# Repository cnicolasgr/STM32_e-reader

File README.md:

# STM32_e-reader
A modest attempt to build an e-reader using a stm32MP1.

> [!CAUTION]
> THIS IS A WORK IN PROGRESS. HACK AROUND AT YOUR OWN RISK.
> I didn't test the board yet and can't be held responsible for any magic smoke 💨

I'm planning to use the [KOReader](https://github.com/koreader/koreader) on OpenSTLinux for the software side, and a modified [epdiy](https://github.com/vroland/epdiy/) driver board for the hardware.
The first version will be using a ED060XC3 screen with a TMA340 touch screen.

Here is the test board:

based on these PCBs from [@martinberlin](https://github.com/martinberlin):

* [epdiy-hardware-versions/versions](https://github.com/martinberlin/epdiy-hardware-versions/tree/main/versions)
* [epdiy-hardware-versions/epdiy-v7-raw](https://github.com/martinberlin/epdiy-hardware-versions/tree/main/epdiy-v7-raw)

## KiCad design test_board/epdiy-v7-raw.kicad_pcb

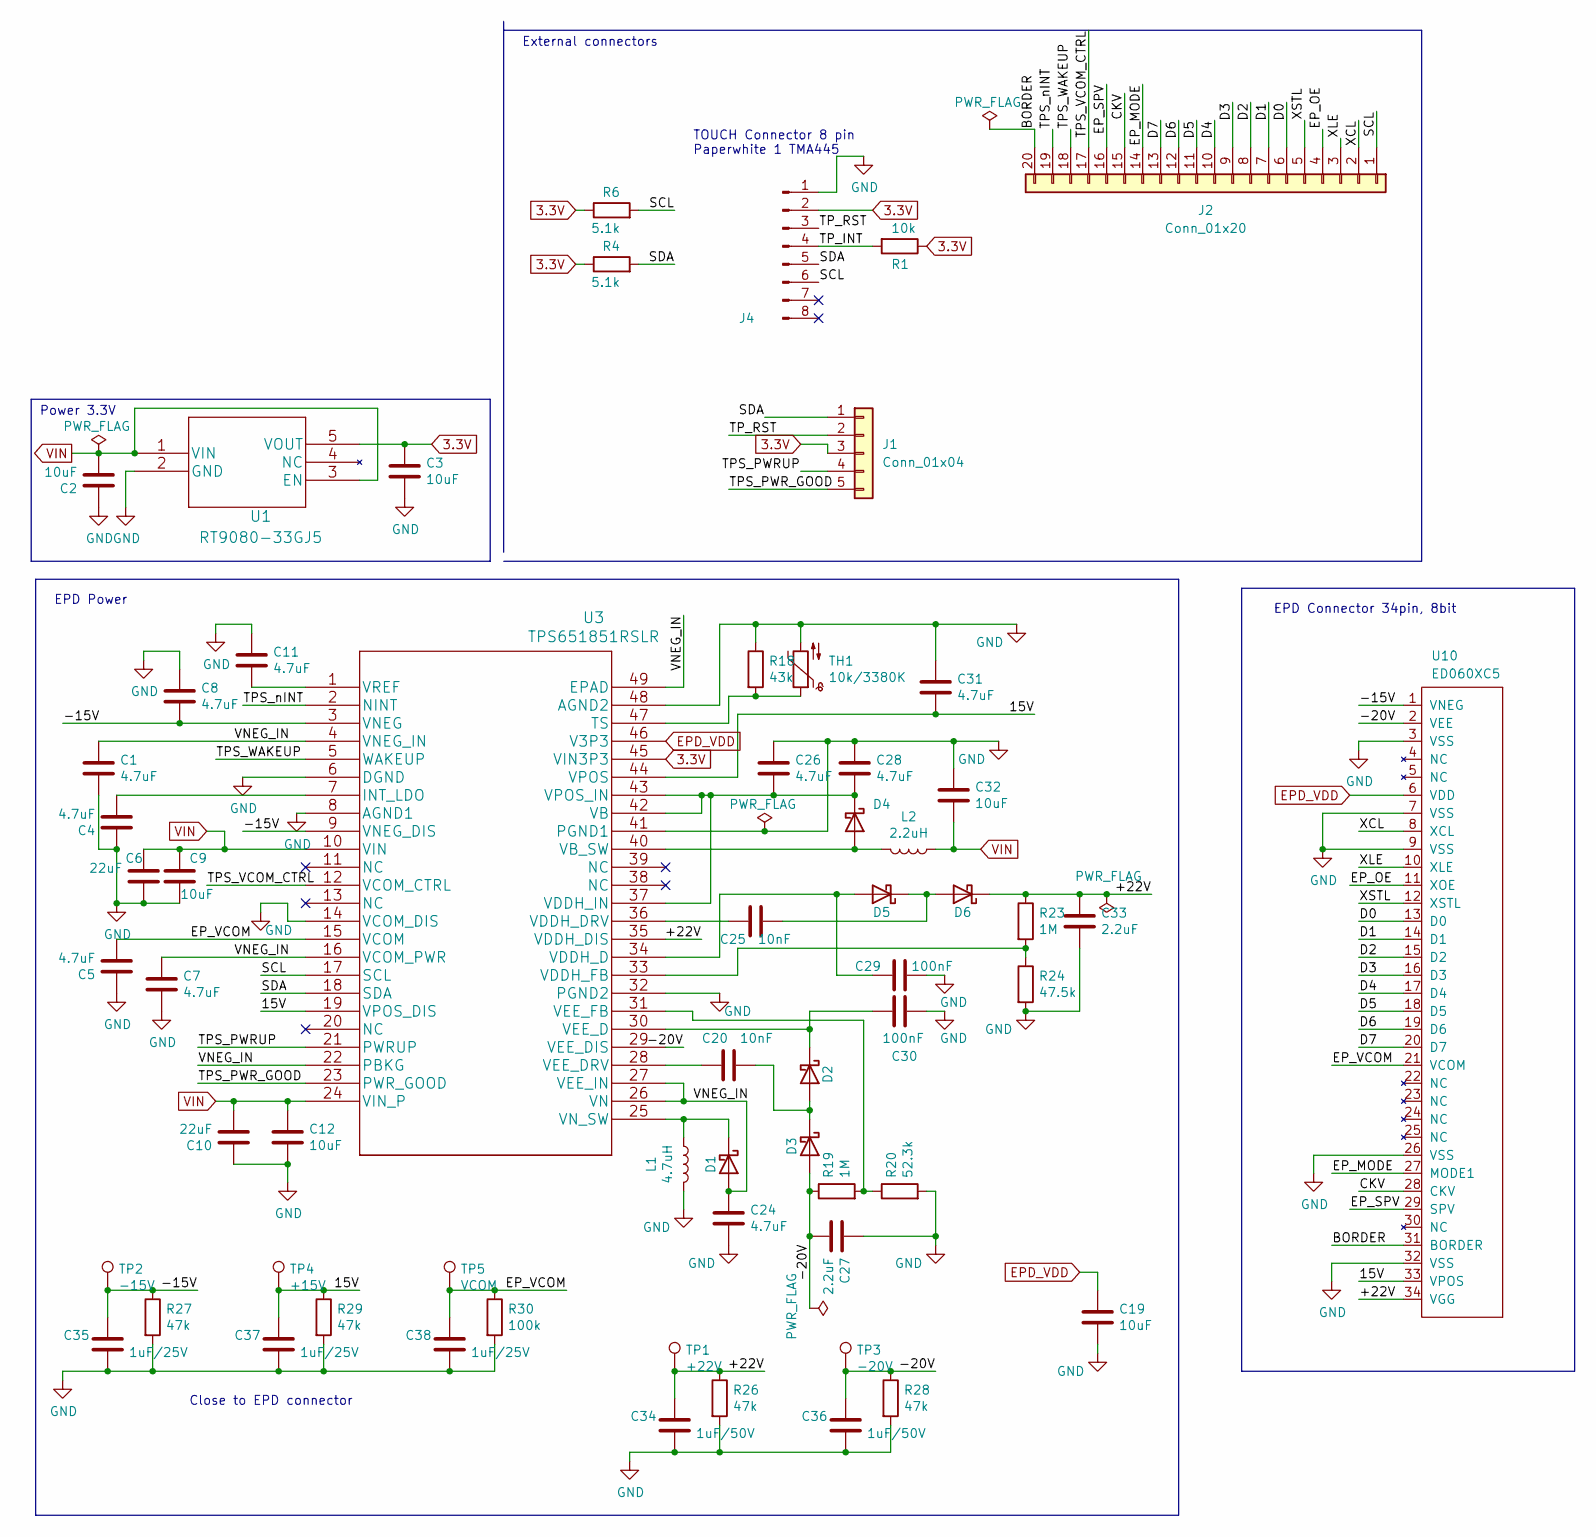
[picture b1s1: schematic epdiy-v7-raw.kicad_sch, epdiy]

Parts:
C1, C4, C5, C7, C8, C11, C24, C26, C28, C31: 4.7uF; C_0805_2012Metric; LCSC C1779
C2, C3, C9, C12, C19, C32: 10uF; C_0805_2012Metric; LCSC C15850
C6, C10: 22uF; C_0805_2012Metric; LCSC C45783
C20, C25: 10nF; C_0805_2012Metric; LCSC C1710
C27, C33: 2.2uF; C_0805_2012Metric; LCSC C49217
C29, C30: 100nF; C_0805_2012Metric; LCSC C49678
C34, C36: 1uF/50V; C_1206_3216Metric; LCSC C1848
C35, C37, C38: 1uF/25V; C_0805_2012Metric; LCSC C28323
D1, D2, D3, D4, D5, D6: MBR0540; D_SOD-123; LCSC C21353
J1: Conn_01x04; PinHeader_1x05_P2.54mm_Vertical
J2: Conn_01x20; PinHeader_1x20_P2.54mm_Vertical
J4: Conn_01x08_Pin; CONN8_FH34SRJ_HIR; LCSC C88372
L1: 4.7uH; L_Taiyo-Yuden_NR-50xx_HandSoldering; LCSC C222947
L2: 2.2uH; L_Taiyo-Yuden_NR-40xx_HandSoldering; LCSC C92959
R1: 10k; R_0603_1608Metric; LCSC C25804
R4, R6: 5.1k; R_0603_1608Metric; LCSC C23186
R18: 43k; R_0603_1608Metric; LCSC C23172
R19, R23: 1M; R_0603_1608Metric; LCSC C22935
R20: 52.3k; R_0603_1608Metric; LCSC C23196
R24: 47.5k; R_0603_1608Metric; LCSC C25819
R26, R27, R28, R29: 47k; R_0603_1608Metric; LCSC C25819
R30: 100k; R_0603_1608Metric; LCSC C25803
TH1: 10k/3380K; R_0603_1608Metric; LCSC C76589
TP1: +22V; TestPoint_Pad_D2.5mm
TP2: -15V; TestPoint_Pad_D2.5mm
TP3: -20V; TestPoint_Pad_D2.5mm
TP4: +15V; TestPoint_Pad_D2.5mm
TP5: VCOM; TestPoint_Pad_D2.5mm
U1: RT9080-33GJ5; TSOT-23-5; LCSC C841192
U3: TPS651851RSLR; LCSC C139292
U10: ED060XC5; X05A20H34G; LCSC C528053

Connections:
3.3V: C3.2, J1.3, J4.2, R1.1, R4.1, R6.1, U1.5 (VOUT), U3.45 (VIN3P3)
/15V: C31.2, C37.1, R29.1, TP4.1, U3.19 (VPOS_DIS), U3.44 (VPOS), U10.33 (VPOS)
/+22V: C33.1, C34.1, D6.1 (K), R23.1, R26.1, TP1.1, U3.35 (VDDH_DIS), U10.34 (VGG)
/-15V: C8.2, C35.1, R27.1, TP2.1, U3.3 (VNEG), U3.9 (VNEG_DIS), U10.1 (VNEG)
/-20V: C27.2, C36.1, D3.2 (A), R19.1, R28.1, TP3.1, U3.29 (VEE_DIS), U10.2 (VEE)
/CKV: J2.15, U10.28 (CKV)
/D0: J2.6, U10.13 (D0)
/D1: J2.7, U10.14 (D1)
/D2: J2.8, U10.15 (D2)
/D3: J2.9, U10.16 (D3)
/D4: J2.10, U10.17 (D4)
/D5: J2.11, U10.18 (D5)
/D6: J2.12, U10.19 (D6)
/D7: J2.13, U10.20 (D7)
/EP_MODE: J2.14, U10.27 (MODE1)
/EP_OE: J2.4, U10.11 (XOE)
/EP_SPV: J2.16, U10.29 (SPV)
/EP_VCOM: C5.2, C38.1, R30.1, TP5.1, U3.15 (VCOM), U10.21 (VCOM)
/SCL: J2.1, J4.6, R6.2, U3.17 (SCL)
/SDA: J1.1, J4.5, R4.2, U3.18 (SDA)
/TPS_PWRUP: J1.4, U3.21 (PWRUP)
/TPS_PWR_GOOD: J1.5, U3.23 (PWR_GOOD)
/TPS_VCOM_CTRL: J2.17, U3.12 (VCOM_CTRL)
/TPS_WAKEUP: J2.18, U3.5 (WAKEUP)
/TPS_nINT: J2.19, U3.2 (NINT)
/TP_INT: J4.4, R1.2
/TP_RST: J1.2, J4.3
/VNEG_IN: C1.1, C7.1, C24.1, D1.2 (A), U3.4 (VNEG_IN), U3.16 (VCOM_PWR), U3.22 (PBKG), U3.26 (VN), U3.27 (VEE_IN), U3.49 (EPAD)
/XCL: J2.2, U10.8 (XCL)
/XLE: J2.3, U10.10 (XLE)
/XSTL: J2.5, U10.12 (XSTL)
EPD_VDD: C19.1, U3.46 (V3P3), U10.6 (VDD)
unnamed: D1.1 (K), L1.1, U3.25 (VN_SW)
unnamed: C20.1, D2.2 (A), D3.1 (K)
unnamed: C30.1, D2.1 (K), U3.30 (VEE_D)
unnamed: D4.2 (A), L2.2, U3.40 (VB_SW)
unnamed: C26.2, C28.2, D4.1 (K), U3.37 (VDDH_IN), U3.42 (VB), U3.43 (VPOS_IN)
unnamed: C29.2, D5.2 (A), U3.34 (VDDH_D)
unnamed: C25.1, D5.1 (K), D6.2 (A)
unnamed: C4.2, U3.7 (INT_LDO)
unnamed: R18.2, TH1.1, U3.47 (TS)
unnamed: C25.2, U3.36 (VDDH_DRV)
unnamed: R23.2, R24.1, U3.33 (VDDH_FB)
unnamed: C20.2, U3.28 (VEE_DRV)
unnamed: R19.2, R20.1, U3.31 (VEE_FB)
unnamed: C11.2, U3.1 (VREF)

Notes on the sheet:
EPD Power
External connectors
Power 3.3V
EPD Connector 34pin, 8bit
TOUCH Connector 8 pin Paperwhite 1 TMA445
Close to EPD connector

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
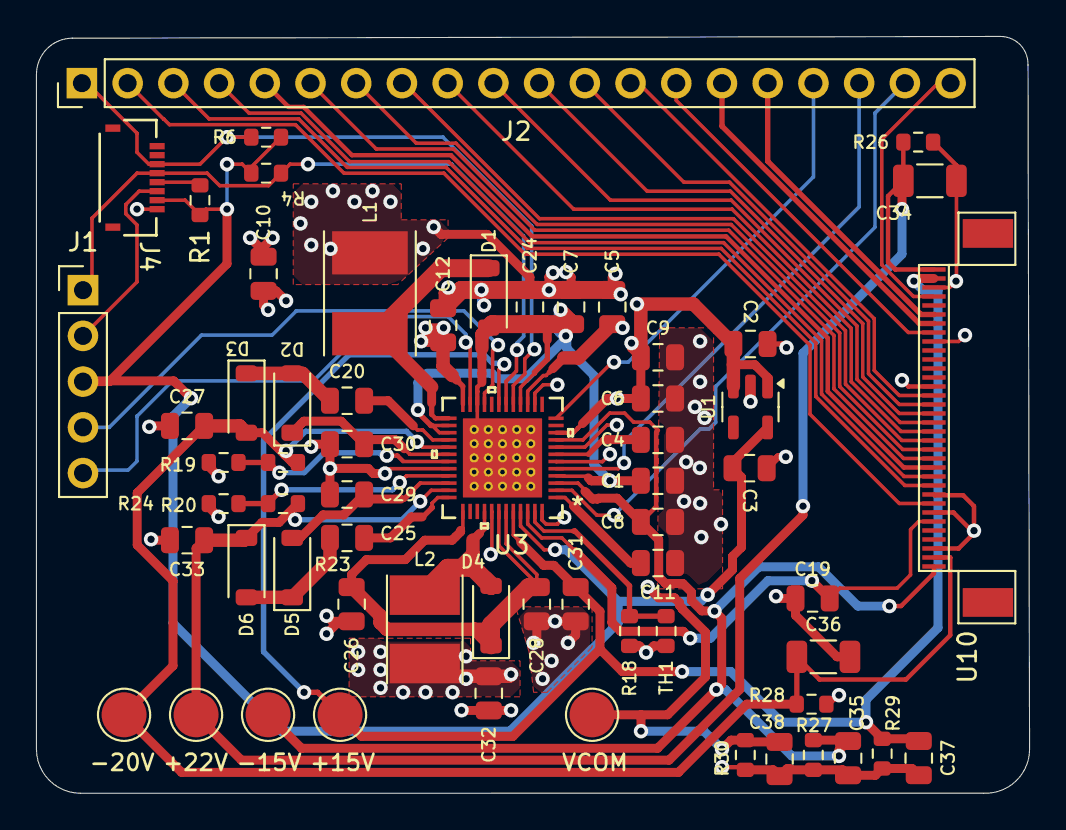
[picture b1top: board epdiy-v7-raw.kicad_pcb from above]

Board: 4 copper layers, 55.2 x 42.0 mm, 62 parts (0 on the bottom side), 49 nets.

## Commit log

2025-03-17 Add test board

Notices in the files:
parts and their libraries:
Copyright 2016 Accelerated Designs. All rights reserved.
